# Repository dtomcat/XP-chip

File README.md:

# OpenXenium JTAG and Flash Memory Chip programmer

**This is based on work done by [kooscode](https://github.com/kooscode/xenium-programmer) and [Ryzee119](https://github.com/ryzee119/openxenium) with modifications to program the bare ICs.  Most of the code here was done by kooscode (please visit the link above).

--------------

## * Read: ["Home Brew" on ORIGINAL XBOX](XBOX.md) - a detailed article on why and how *

The tools in this repo will allow you to use a Raspberry PI to program the CPLD and Flash Memory chips of the OpenXenium via Jtag and a custom 4-bit bus NOR Flash programming protocol.
Original project mentioned above allowed the use of an Onion Omega2+... This has been removed for this project. 

### Raspberry PI:
- This has only been tested on PI Zero W and PI 3B+ models so far.

https://www.pishop.us/product/raspberry-pi-zero-w/

-------------
## INSTALLING THE XENIUM PROGRAMMER

- After the OS has been written to your SD card, insert SD card into PC.
    - Add the following to the last line in "config.txt":   `enable_uart=1`
        - This is required to allow the PWR LED to function properly.
- Save edit and eject SD Card.  Insert SD card into Pi and boot up.
- Connect to the PI via SSH or Serial terminal
- If git is not installed, you need to install it:
    - `sudo apt-get install git`
- Clone this repo by running: `git clone https://github.com/dtomcat/XP-chip.git`
- Change to program directory: `cd XP-chip`
- Fix permission on install file:  `chmod 755 install`
- Then run: `./install`
- Setup service to listen for button presses:
    - `sudo cp xeniumCHIP.service /etc/systemd/system/xeniumCHIP.service`
    - `sudo systemctl daemon-reload`
    - `sudo systemctl enable xeniumCHIP`
    - `sudo service xeniumCHIP start`

## UPDATING XENIUM PROGRAMMER

- Connect to the PI via SSH or Serial terminal 
- Pull the latest code with: `git pull`
- Then run: `./install` 

-------------
## PROGRAMMING THE XENIUM CPLD AND/OR FLASH MEMORY (STANDALONE)

- After the PI has fully booted and the green led is on...
    - Press the FIRST button to program both ICs. (both ICs must be inserted into their respective sockets)
    - Hold the FIRST button to program the CPLD with the Bit Bang firmware. (Only the CPLD must be inserted, Flash is optional)
    - Press the SECOND button to program the flash chip. (**The CPLD must be present and have the Bit Bang firmware loaded or this will fail.  Both Chips must be inserted)
    - Press the THIRD button to program the CPLD with the OpenXenium Firmware. (Only the CPLD must be inserted, Flash is optional)
    - Press the FOURTH button to clear any errors.
    - Hold the FOURTH button to shutdown the Raspberry Pi.

-------------
## PROGRAMMING THE XENIUM CPLD AND/OR FLASH MEMORY (SSH/SERIAL)
This is good to do if you keep getting an error trying to program the chips. (Red LED remains on)

- Connect to the PI via SSH or Serial terminal
- Change dir to XP-chip
- You can program CPLD and FLASH in one single step. (Both must be inserted into their respective sockets)
    - Run: `./xenium-programmer-smd`
- You can program just the CPLD in one two ways. (Only the CPLD needs to be inserted into it's socket)
    - To program the Bit Bang firmware: 
        - Run: `./BitBangOnly`
    - To program the OpenXenium firmware: 
        - Run: `./OX-Only_SMD`
- You can program just the Flash. (Both must be inserted into their respective sockets, and the CPLD MUST have the Bit Bang Firmware loaded)
    - Run: `./FlashOnly`

-------------

### PC BOARD

Huge thanks to James Bolding for the Original Eagle PCB hardware design!
This PCB design is based on his original work and the work of Ryzee119's OpenXenium.  

- You can use the FREE Eagle PCB to load this up or just use the gerber files to have the PCB made at OSH Park!

--------------

### PARTS NOT LISTED IN BOM
The two sockets were sourced from Ebay (linked below).  They may be available from another source, but the design is based off these particular sockets.  If you decide to go with another source, they may not line up/work.

- CPLD Socket: [QFP64 TQFP64 to DIP64 Pitch 0.5mm IC Programmer Adapter Test Socket](https://www.ebay.com/itm/172825294343)
    
- Flash Socket: [TSOP48 To DIP48 Double Contact Gold Plating Universal IC Programm Socket Adapter](https://www.ebay.com/itm/402764448631)

-------------
## CREDITS

- Koos du Preez - Creator (kdupreez@hotmail.com - Comments, improvements, critique, etc. is welcome!)
- Dtomcat - CHIP programmer PCB design.
- James Bolding - Orignal hardware design and PCB!
- Ryzee119 -  OpenXenium Firmware and hardware and all round awesomeness!
- XC3SPROG - Not sure who to thank here, but the source code was pivotal in making this work!

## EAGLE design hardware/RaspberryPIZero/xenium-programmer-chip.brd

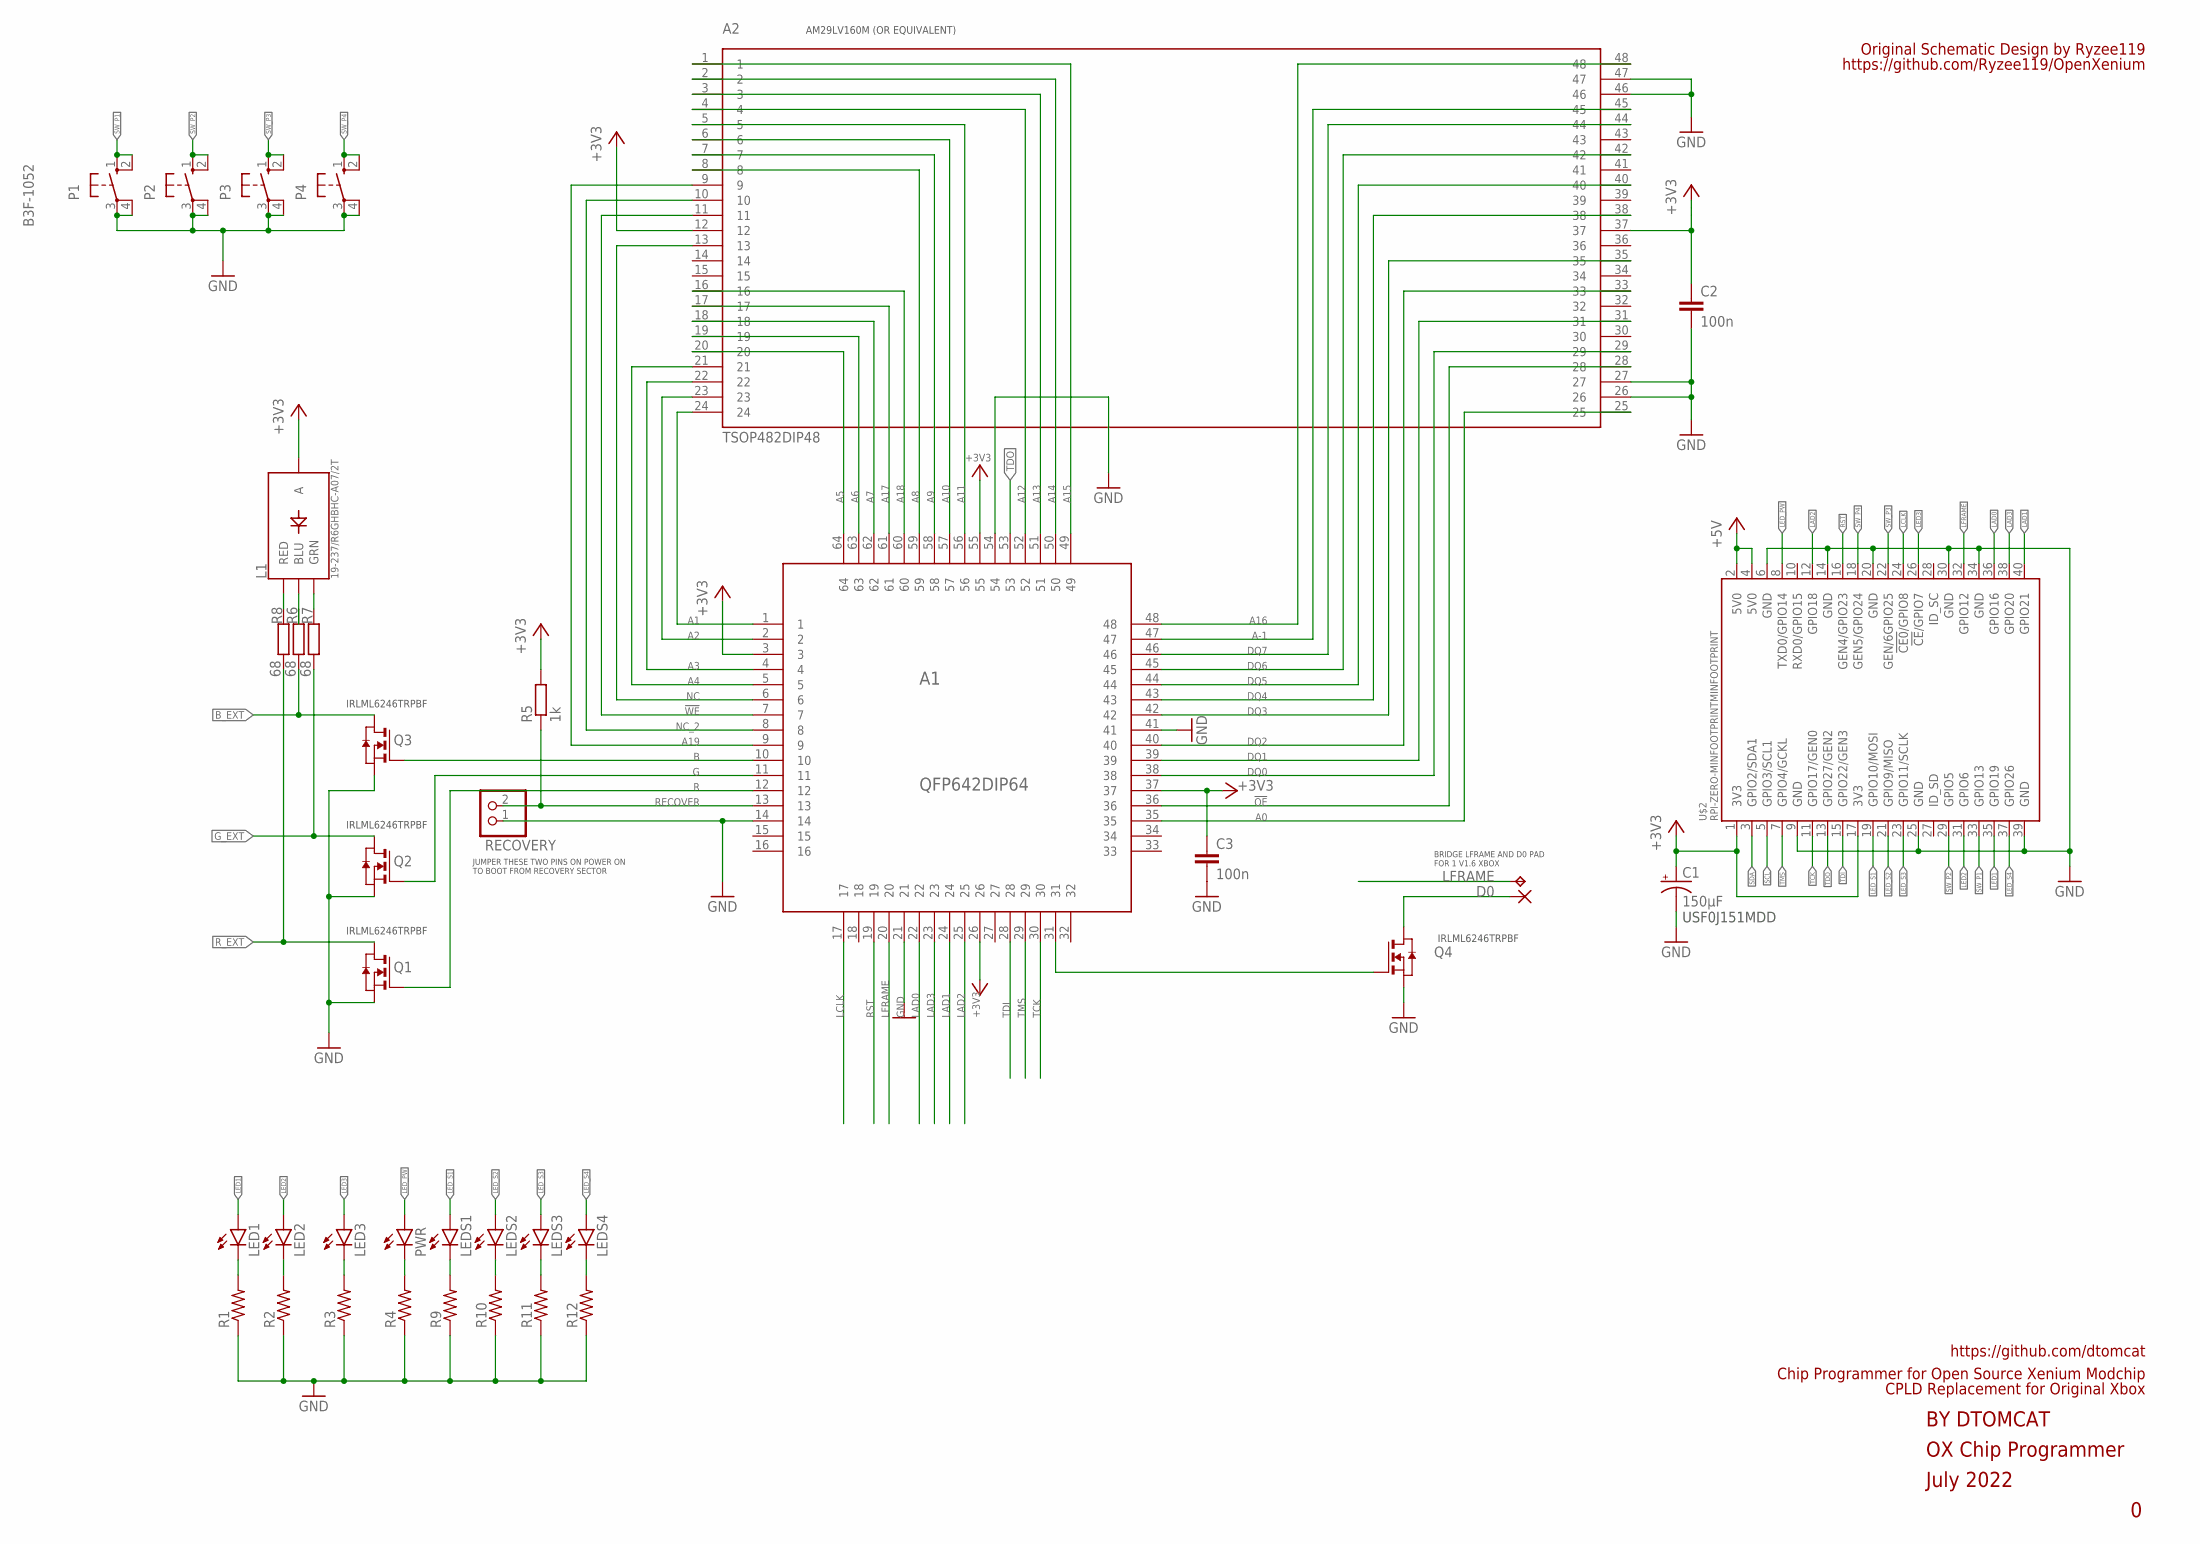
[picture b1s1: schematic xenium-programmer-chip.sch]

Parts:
A1: QFP642DIP64
A2: TSOP482DIP48
C1: 150µF; E3,5-8
C2, C3: 100n; C0603
D0: SMD2; SMD1,27-2,54
L1: 19-237/R6GHBHC-A07/2T; 4-SMD-R6GHBHC
LED1, LED2, LED3: LEDCHIPLED_1206; CHIPLED_1206
LEDS1, LEDS2, LEDS3, LEDS4: LEDCHIPLED_1206; CHIPLED_1206
P1, P2, P3, P4: B3F-1052; B3F-10XX
PWR: LEDCHIPLED_1206; CHIPLED_1206
Q1, Q2, Q3, Q4: 310mA/60V/1.6Ω; SOT-23
R1, R2, R3, R4, R9, R10, R11, R12: R-US_R1206; R1206
R5: 1k; R0603
R6, R7, R8: 68; R0603
RECOVERY: PINHD-1X2; 1X02
TP1: TPTP13SQ; TP13SQ
U$2: RPI-ZERO-MINFOOTPRINTMINFOOTPRINT; RASP_PI_ZERO_MIN

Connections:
5V0@2: U$2.2 (5V0), U$2.4 (5V0)
!OE: A1.36, A2.28
!WE: A1.7, A2.11
+3V3: A1.3, A1.26, A1.37, A1.55, A2.12, A2.37, C1.+, C2.1, C3.1, L1.P$2 (A), R5.2, U$2.1 (3V3), U$2.17 (3V3)
A0: A1.35, A2.25
A1: A1.1, A2.24
A2: A1.2, A2.23
A3: A1.4, A2.22
A4: A1.5, A2.21
A5: A1.64, A2.20
A6: A1.63, A2.19
A7: A1.62, A2.18
A8: A1.59, A2.8
A9: A1.58, A2.7
A10: A1.57, A2.6
A11: A1.56, A2.5
A12: A1.52, A2.4
A13: A1.51, A2.3
A14: A1.50, A2.2
A15: A1.49, A2.1
A16: A1.48, A2.48
A17: A1.61, A2.17
A18: A1.60, A2.16
A19: A1.9, A2.9
A-1: A1.47, A2.45
B: A1.10, Q3.3 (G)
BLUE: L1.P$4 (BLU), R6.1
B_EXT: Q3.1 (D), R6.2
DQ0: A1.38, A2.29
DQ1: A1.39, A2.31
DQ2: A1.40, A2.33
DQ3: A1.42, A2.35
DQ4: A1.43, A2.38
DQ5: A1.44, A2.40
DQ6: A1.45, A2.42
DQ7: A1.46, A2.44
G: A1.11, Q2.3 (G)
GND: A1.14, A1.21, A1.41, A1.54, A2.26, A2.27, A2.46, A2.47, C1.-, C2.2, C3.2, P1.3, P1.4 (P1), P2.3, P2.4 (P1), P3.3, P3.4 (P1), P4.3, P4.4 (P1), Q1.2 (S), Q2.2 (S), Q3.2 (S), Q4.2 (S), R1.1, R2.1, R3.1, R4.1, R9.1, R10.1, R11.1, R12.1, RECOVERY.1, U$2.6 (GND), U$2.9 (GND), U$2.14 (GND), U$2.20 (GND), U$2.25 (GND), U$2.30 (GND), U$2.34 (GND), U$2.39 (GND)
GREEN: L1.P$3 (GRN), R7.1
G_EXT: Q2.1 (D), R7.2
LAD0: A1.22, U$2.36 (GPIO16)
LAD1: A1.24, U$2.40 (GPIO21)
LAD2: A1.25, U$2.12 (GPIO18)
LAD3: A1.23, U$2.38 (GPIO20)
LCLK: A1.17, U$2.24 (!CE0!/GPIO8)
LED1: LED1.A, U$2.35 (GPIO19)
LED2: LED2.A, U$2.31 (GPIO6)
LED3: LED3.A, U$2.26 (!CE!/GPIO7)
LED_PW: PWR.A, U$2.8 (TXD0/GPIO14)
LED_S1: LEDS1.A, U$2.19 (GPIO10/MOSI)
LED_S2: LEDS2.A, U$2.21 (GPIO9/MISO)
LED_S3: LEDS3.A, U$2.23 (GPIO11/SCLK)
LED_S4: LEDS4.A, U$2.37 (GPIO26)
LFRAME: A1.20, TP1.TP, U$2.32 (GPIO12)
unnamed: LED1.C, R1.2
unnamed: LEDS1.C, R9.2
unnamed: LED2.C, R2.2
unnamed: LED3.C, R3.2
unnamed: PWR.C, R4.2
unnamed: LEDS2.C, R10.2
unnamed: LEDS3.C, R11.2
unnamed: LEDS4.C, R12.2
unnamed: A1.31, Q4.3 (G)
unnamed: D0.1, Q4.1 (D)
NC: A1.6, A2.13
NC_2: A1.8, A2.10
R: A1.12, Q1.3 (G)
RECOVER: A1.13, R5.1, RECOVERY.2
RED: L1.P$1 (RED), R8.1
RST: A1.19, U$2.16 (GEN4/GPIO23)
R_EXT: Q1.1 (D), R8.2
SCL: U$2.5 (GPIO3/SCL1)
SDA: U$2.3 (GPIO2/SDA1)
SW_P1: P1.1 (S), P1.2 (S1), U$2.33 (GPIO13)
SW_P2: P2.1 (S), P2.2 (S1), U$2.29 (GPIO5)
SW_P3: P3.1 (S), P3.2 (S1), U$2.22 (GEN/6GPIO25)
SW_P4: P4.1 (S), P4.2 (S1), U$2.18 (GEN5/GPIO24)
TCK: A1.30, U$2.11 (GPIO17/GEN0)
TDI: A1.28, U$2.15 (GPIO22/GEN3)
TDO: A1.53, U$2.13 (GPIO27/GEN2)
TMS: A1.29, U$2.7 (GPIO4/GCKL)

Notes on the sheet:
OX Chip Programmer
July 2022
BY DTOMCAT
Chip Programmer for Open Source Xenium Modchip
https://github.com/dtomcat
BRIDGE LFRAME AND D0 PAD FOR 1 V1.6 XBOX
JUMPER THESE TWO PINS ON POWER ON TO BOOT FROM RECOVERY SECTOR
IRLML6246TRPBF
AM29LV160M (OR EQUIVALENT)
CPLD Replacement for Original Xbox
Original Schematic Design by Ryzee119
https://github.com/Ryzee119/OpenXenium
USF0J151MDD

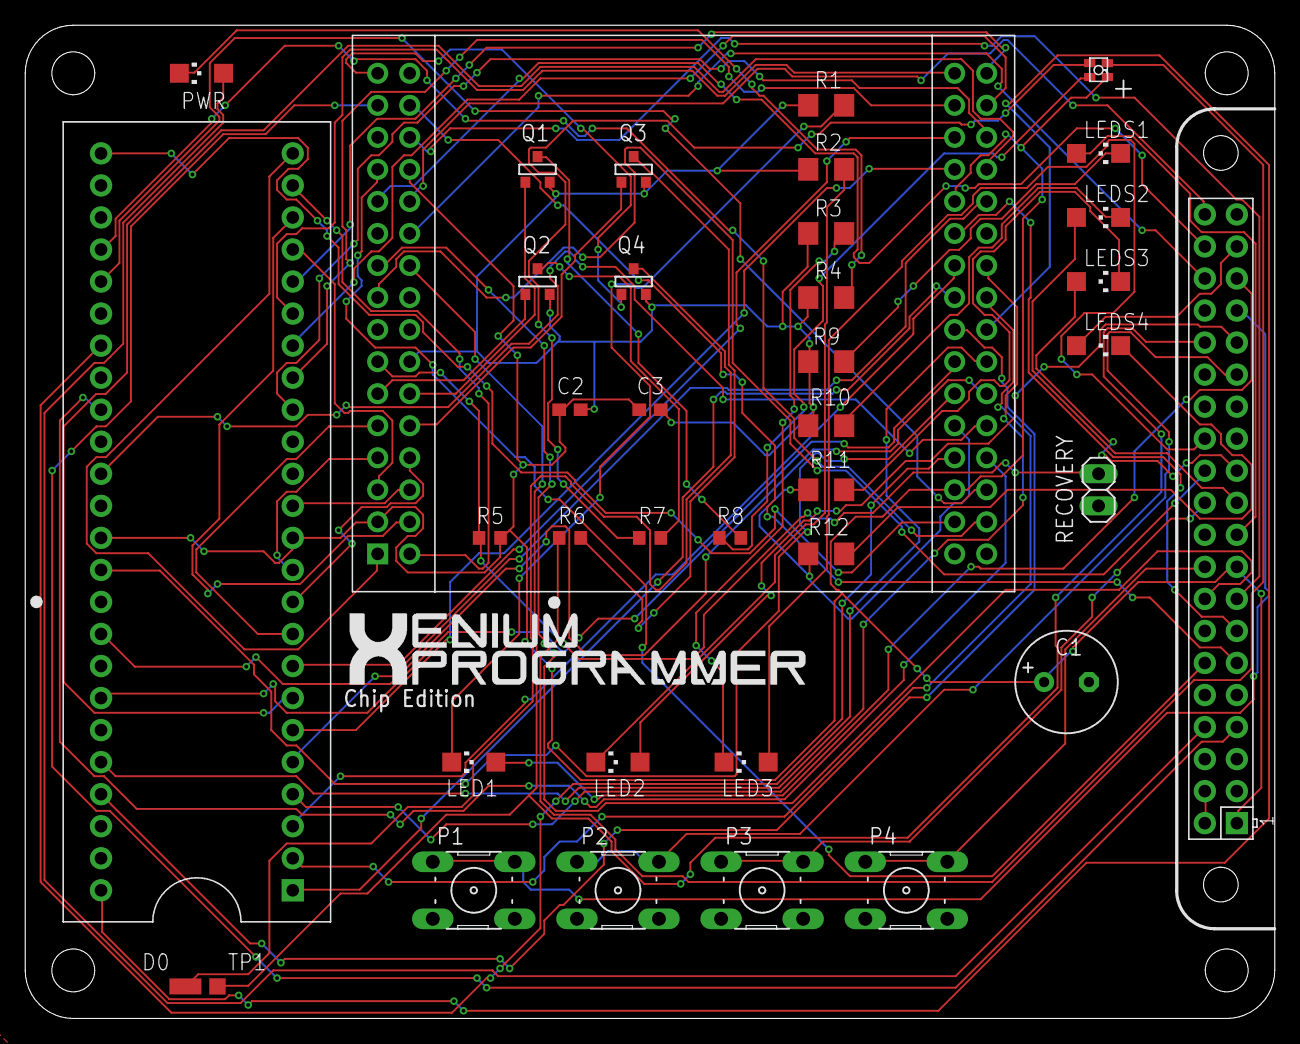
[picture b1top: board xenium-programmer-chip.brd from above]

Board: 2 copper layers, 99.1 x 78.7 mm, 39 parts (1 on the bottom side), 79 nets.

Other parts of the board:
U$1: OSHW_8MM

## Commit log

2023-01-05 Initial Upload
2023-01-06 small updates to path and function
2023-01-06 update Readme for current project and add hardware/images
2023-01-06 update images to Rev 1
2023-01-06 fix permissions
2023-01-07 Update instructions
2023-01-07 fix command
2023-01-16 update for new OS (compatible wiringpi)
2023-01-16 Spelling
2023-01-16 undo previous update
2023-01-16 Fix button functions
2023-01-16 added GIT install
2026-01-09 Update install
    Updated to fix wiringpi issues since drogon.net took it down.

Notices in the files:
hardware/RaspberryPIZero/xenium-programmer-chip.brd:
Released under
CERN OHL v1.2
